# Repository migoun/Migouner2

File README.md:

# Migouner2
Second Mechanical Keyboard. This is a follow up of a keyboard, built 6 years ago: https://github.com/migoun/mechanical_keyboard_mac

Changes:
- STM32 MCU instead of Atmel Chip
- Addressable RGB LEDs backlight for each key (therefore the STM32)
- USB Micro port, to make this as low profile as possible
- Using JLCs Assembly service for one side of the board. 6 years ago, that didn't exist - or at least not for free. So i soldered everything back then
- First tries with printed 3D casings. Eventually CNC machining at a later stage

This time i start with a dev board, instead the whole keyboard:

**Front**

**Back**

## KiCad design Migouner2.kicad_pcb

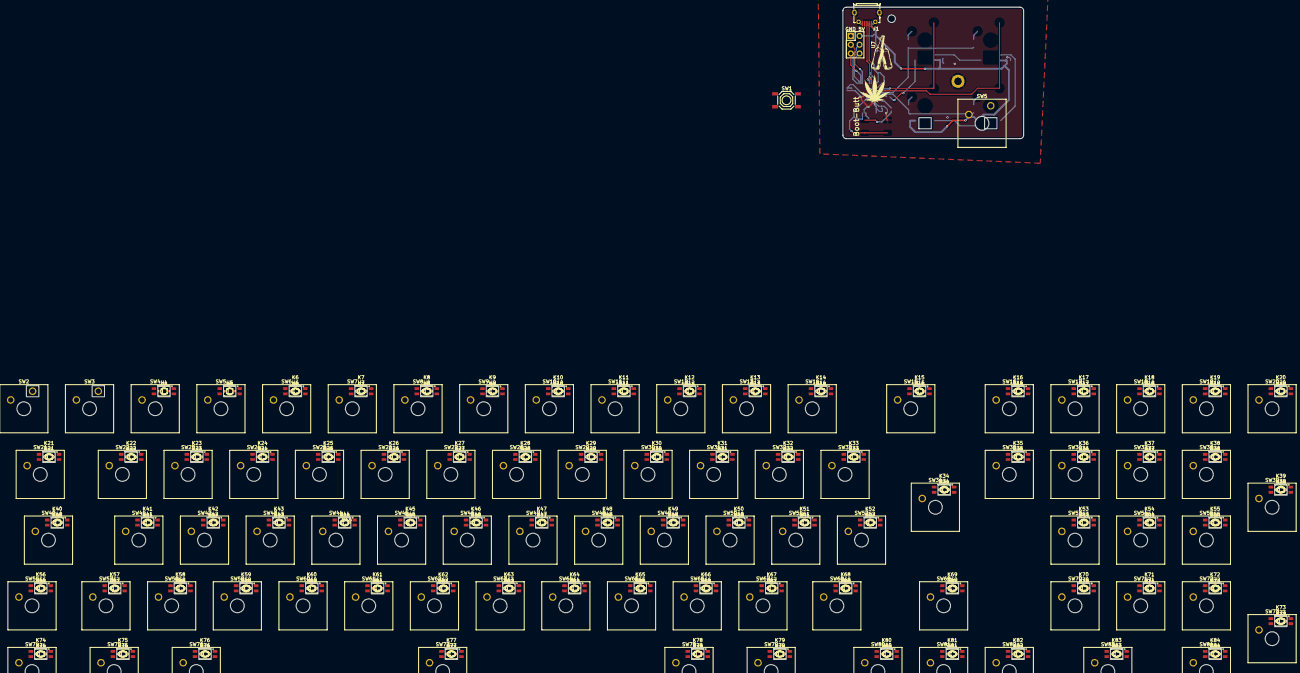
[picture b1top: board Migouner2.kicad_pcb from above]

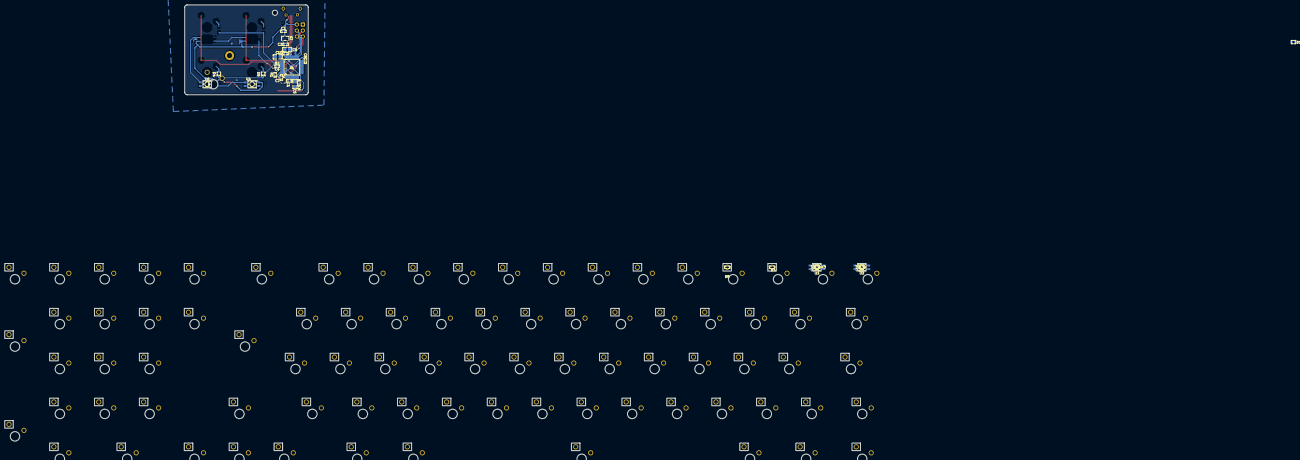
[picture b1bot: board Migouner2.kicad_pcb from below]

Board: 2 copper layers, 365.6 x 189.1 mm, 355 parts (27 on the bottom side), 204 nets.

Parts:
C1, C7, C8, C10: 100nF; C0402
C2, C3, C6: 1uF; C0402
C4, C9: 4.7uF; C0805
C5: 10nF; C0805
D1: ESDA7P60-1U1M; D1610-RD
D2, D4, D5, D6, D7, D8, D9, D10, D11, D12, D13, D14, D15, D16, D17, D18, D19, D20, D21, D23, D24, D25, D26, D27, D28, D29, D30, D31, D32, D33, D34, D35, D36, D37, D38, D39, D40, D42, D43, D44, D45, D46, D47, D48, D49, D50, D51, D52, D53, D54, D55, D56, D58, D59, D60, D61, D62, D63, D64, D65, D66, D67, D68, D69, D70, D71, D72, D73, D74, D76, D77, D78, D79, D80, D81, D82, D83, D84: A; SOD-323_L1.8-W1.3-LS2.5-RD
D3, D22, D41, D57, D75: S; SOD-323_L1.8-W1.3-LS2.5-RD
D4#2: W; SOD-323_L1.8-W1.3-LS2.5-RD
D5#2: D; SOD-323_L1.8-W1.3-LS2.5-RD
J1: USB_B_Micro; MICRO-USB-SMD_MICROXNJ
K2, K3, K4, K5, K6, K7, K8, K9, K10, K11, K12, K13, K14, K15, K16, K17, K18, K19, K20, K21, K22, K23, K24, K25, K26, K27, K28, K29, K30, K31, K32, K33, K34, K35, K36, K37, K38, K39, K40, K41, K42, K43, K44, K45, K46, K47, K48, K49, K50, K51, K52, K53, K54, K55, K56, K57, K58, K59, K60, K61, K62, K63, K64, K65, K66, K67, K68, K69, K70, K71, K72, K73, K74, K75, K76, K77, K78, K79, K80, K81, K82, K83, K84: 100nF; C0402
R1: 10K; R0402
R2: 470; R0402
SW1: Boot Switch; SW-SMD_4P-L5.1-W5.1-P3.70-LS6.5-TL-2
SW2: Esc; SW_Cherry_MX_1.00u_Plate
SW3: ! 1; SW_Cherry_MX_1.00u_Plate
SW4: " 2; SW_Cherry_MX_1.00u_Plate
SW5: £ 3; SW_Cherry_MX_1.00u_Plate
SW5#2, SW23: W; SW_Cherry_MX_1.00u_Plate
SW6: $ 4; SW_Cherry_MX_1.00u_Plate
SW7: % 5; SW_Cherry_MX_1.00u_Plate
SW8: ^ 6; SW_Cherry_MX_1.00u_Plate
SW9: & 7; SW_Cherry_MX_1.00u_Plate
SW10: * 8; SW_Cherry_MX_1.00u_Plate
SW11: ( 9; SW_Cherry_MX_1.00u_Plate
SW12: ) 0; SW_Cherry_MX_1.00u_Plate
SW13: _ -; SW_Cherry_MX_1.00u_Plate
SW14: + =; SW_Cherry_MX_1.00u_Plate
SW15: Backspace; SW_Cherry_MX_2.00u_Plate
SW16: Insert; SW_Cherry_MX_1.00u_Plate
SW17: %; SW_Cherry_MX_1.00u_Plate
SW18: /; SW_Cherry_MX_1.00u_Plate
SW19: *; SW_Cherry_MX_1.00u_Plate
SW20: -; SW_Cherry_MX_1.00u_Plate
SW21: Tab; SW_Cherry_MX_1.50u_Plate
SW22: Q; SW_Cherry_MX_1.00u_Plate
SW24: E; SW_Cherry_MX_1.00u_Plate
SW25: R; SW_Cherry_MX_1.00u_Plate
SW26: T; SW_Cherry_MX_1.00u_Plate
SW27: Y; SW_Cherry_MX_1.00u_Plate
SW28: U; SW_Cherry_MX_1.00u_Plate
SW29: I; SW_Cherry_MX_1.00u_Plate
SW30: O; SW_Cherry_MX_1.00u_Plate
SW31: P; SW_Cherry_MX_1.00u_Plate
SW32: { [; SW_Cherry_MX_1.00u_Plate
SW33: } ]; SW_Cherry_MX_1.00u_Plate
SW34: Enter; SW_Cherry_MX_ISOEnter_Plate
SW35: Delete; SW_Cherry_MX_1.00u_Plate
SW36: 7 Home; SW_Cherry_MX_1.00u_Plate
SW37: 8 ↑; SW_Cherry_MX_1.00u_Plate
SW38: 9 PgUp; SW_Cherry_MX_1.00u_Plate
SW39: +; SW_Cherry_MX_2.00u_Vertical_Plate
SW40: Caps Lock; SW_Cherry_MX_1.75u_Plate
SW41: A; SW_Cherry_MX_1.00u_Plate
SW42: S; SW_Cherry_MX_1.00u_Plate
SW43: D; SW_Cherry_MX_1.00u_Plate
SW44: F; SW_Cherry_MX_1.00u_Plate
SW45: G; SW_Cherry_MX_1.00u_Plate
SW46: H; SW_Cherry_MX_1.00u_Plate
SW47: J; SW_Cherry_MX_1.00u_Plate
SW48: K; SW_Cherry_MX_1.00u_Plate
SW49: L; SW_Cherry_MX_1.00u_Plate
SW50: : ;; SW_Cherry_MX_1.00u_Plate
SW51: @ '; SW_Cherry_MX_1.00u_Plate
SW52: ~ #; SW_Cherry_MX_1.00u_Plate
SW53: 4 ←; SW_Cherry_MX_1.00u_Plate
SW54: 5; SW_Cherry_MX_1.00u_Plate
SW55: 6 →; SW_Cherry_MX_1.00u_Plate
SW56, SW68: Shift; SW_Cherry_MX_1.25u_Plate
SW57: | \; SW_Cherry_MX_1.00u_Plate
SW58: Z; SW_Cherry_MX_1.00u_Plate
SW59: X; SW_Cherry_MX_1.00u_Plate
SW60: C; SW_Cherry_MX_1.00u_Plate
SW61: V; SW_Cherry_MX_1.00u_Plate
SW62: B; SW_Cherry_MX_1.00u_Plate
SW63: N; SW_Cherry_MX_1.00u_Plate
SW64: M; SW_Cherry_MX_1.00u_Plate
SW65: < ,; SW_Cherry_MX_1.00u_Plate
SW66: > .; SW_Cherry_MX_1.00u_Plate
SW67: ? /; SW_Cherry_MX_1.00u_Plate
SW69: ↑; SW_Cherry_MX_1.00u_Plate
SW70: 1 End; SW_Cherry_MX_1.00u_Plate
SW71: 2 ↓; SW_Cherry_MX_1.00u_Plate
SW72: 3 PgDn; SW_Cherry_MX_1.00u_Plate
SW73: Enter; SW_Cherry_MX_2.00u_Vertical_Plate
SW74: Ctrl; SW_Cherry_MX_1.25u_Plate
SW75: Win; SW_Cherry_MX_1.25u_Plate
SW76: Alt; SW_Cherry_MX_1.25u_Plate
SW77: SW_Cherry_MX_6.25u_Plate
SW78: AltGr; SW_Cherry_MX_1.25u_Plate
SW79: Fn; SW_Cherry_MX_1.25u_Plate
SW80: ←; SW_Cherry_MX_1.00u_Plate
SW81: ↓; SW_Cherry_MX_1.00u_Plate
SW82: →; SW_Cherry_MX_1.00u_Plate
SW83: 0 Ins; SW_Cherry_MX_2.00u_Plate
SW84: . Del; SW_Cherry_MX_1.00u_Plate
U2, U3, U4, U5, U6, U7, U8, U9, U10, U11, U12, U13, U14, U15, U16, U17, U18, U19, U20, U21, U22, U23, U24, U25, U26, U27, U28, U29, U30, U31, U32, U33, U34, U35, U36, U37, U38, U39, U40, U41, U42, U43, U44, U45, U46, U47, U48, U49, U50, U51, U52, U53, U54, U55, U56, U57, U58, U59, U60, U61, U62, U63, U64, U65, U66, U67, U68, U69, U70, U71, U72, U73, U74, U75, U76, U77, U78, U79, U80, U81, U82, U83, U84: LED-SMD_L3.2-W2.8-TR
U4#2: D; LED-SMD_L3.2-W2.8-TR
U6#2: W; LED-SMD_L3.2-W2.8-TR
U7#2: ZX-PZ2.54-2-5PZZ; HDR-TH_6P-P2.54-V-M-R2-C3-S2.54-1
X1: STM32F072CBT6; LQFP-48_L7.0-W7.0-P0.50-LS9.0-BL
X2: XC6206P332MR-G; SOT-23-3_L2.9-W1.6-P1.90-LS2.8-BR

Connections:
+3.3V: C3.1, C4.1, C5.1, C6.1, C7.1, C8.1, C9.1, C10.1, SW1.1 (A), SW1.2 (B), X1.1 (VBAT), X1.9 (VDDA), X1.24 (VDD), X1.36 (VDDIO2), X1.48 (VDD), X2.2 (VO)
+5V: C2.1, D1.1 (C), J1.1 (VBUS), K2.1, K3.1, K4.1, K5.1, K6.1, K7.1, K8.1, K9.1, K10.1, K11.1, K12.1, K13.1, K14.1, K15.1, K16.1, K17.1, K18.1, K19.1, K20.1, K21.1, K22.1, K23.1, K24.1, K25.1, K26.1, K27.1, K28.1, K29.1, K30.1, K31.1, K32.1, K33.1, K34.1, K35.1, K36.1, K37.1, K38.1, K39.1, K40.1, K41.1, K42.1, K43.1, K44.1, K45.1, K46.1, K47.1, K48.1, K49.1, K50.1, K51.1, K52.1, K53.1, K54.1, K55.1, K56.1, K57.1, K58.1, K59.1, K60.1, K61.1, K62.1, K63.1, K64.1, K65.1, K66.1, K67.1, K68.1, K69.1, K70.1, K71.1, K72.1, K73.1, K74.1, K75.1, K76.1, K77.1, K78.1, K79.1, K80.1, K81.1, K82.1, K83.1, K84.1, U4#2.1 (VDD), U6#2.1 (VDD), U7#2.2, U74.1 (VDD), U75.1 (VDD), U76.1 (VDD), U77.1 (VDD), U78.1 (VDD), U79.1 (VDD), U80.1 (VDD), U81.1 (VDD), U82.1 (VDD), U83.1 (VDD), U84.1 (VDD), X2.3 (VI)
/Keyboard Matrix/Col0: SW2.1, SW21.1, SW40.1, SW56.1, SW74.1, X1.41 (PB5)
/Keyboard Matrix/Col1: SW3.1, SW5#2.1, SW22.1, SW41.1, SW57.1, SW75.1, X1.40 (PB4)
/Keyboard Matrix/Col2: SW4.1, SW23.1, SW42.1, SW58.1, SW76.1, X1.39 (PB3)
/Keyboard Matrix/Col3: SW5.1, SW24.1, SW43.1, SW59.1, X1.38 (PA15)
/Keyboard Matrix/Col4: SW6.1, SW25.1, SW44.1, SW60.1, X1.37 (PA14)
/Keyboard Matrix/Col5: SW7.1, SW26.1, SW45.1, SW61.1, X1.34 (PA13)
/Keyboard Matrix/Col6: SW8.1, SW27.1, SW46.1, SW62.1, SW77.1, X1.31 (PA10)
/Keyboard Matrix/Col7: SW9.1, SW28.1, SW47.1, SW63.1, X1.30 (PA9)
/Keyboard Matrix/Col8: SW10.1, SW29.1, SW48.1, SW64.1, X1.29 (PA8)
/Keyboard Matrix/Col9: SW11.1, SW30.1, SW49.1, SW65.1, X1.28 (PB15)
/Keyboard Matrix/Col10: SW12.1, SW31.1, SW50.1, SW66.1, SW78.1, X1.27 (PB14)
/Keyboard Matrix/Col11: SW13.1, SW32.1, SW51.1, SW67.1, SW79.1, X1.26 (PB13)
/Keyboard Matrix/Col12: SW14.1, SW33.1, SW52.1, SW68.1, SW80.1, X1.25 (PB12)
/Keyboard Matrix/Col13: SW15.1, SW34.1, SW69.1, SW81.1, X1.11 (PA1)
/Keyboard Matrix/Col14: SW16.1, SW35.1, SW82.1, X1.12 (PA2)
/Keyboard Matrix/Col15: SW17.1, SW36.1, SW53.1, SW70.1, SW83.1, X1.13 (PA3)
/Keyboard Matrix/Col16: SW18.1, SW37.1, SW54.1, SW71.1, X1.14 (PA4)
/Keyboard Matrix/Col17: SW19.1, SW38.1, SW55.1, SW72.1, SW84.1, X1.15 (PA5)
/Keyboard Matrix/Col18: SW20.1, SW39.1, SW73.1, X1.16 (PA6)
/Keyboard Matrix/Row0: D2.1, D3.1, D4.1, D5.1, D6.1, D7.1, D8.1, D9.1, D10.1, D11.1, D12.1, D13.1, D14.1, D15.1, D16.1, D17.1, D18.1, D19.1, D20.1, X1.10 (PA0)
/Keyboard Matrix/Row1: D4#2.1, D5#2.1, D21.1, D22.1, D23.1, D24.1, D25.1, D26.1, D27.1, D28.1, D29.1, D30.1, D31.1, D32.1, D33.1, D34.1, D35.1, D36.1, D37.1, D38.1, D39.1, X1.46 (PB9)
/Keyboard Matrix/Row2: D40.1, D41.1, D42.1, D43.1, D44.1, D45.1, D46.1, D47.1, D48.1, D49.1, D50.1, D51.1, D52.1, D53.1, D54.1, D55.1, X1.45 (PB8)
/Keyboard Matrix/Row3: D56.1, D57.1, D58.1, D59.1, D60.1, D61.1, D62.1, D63.1, D64.1, D65.1, D66.1, D67.1, D68.1, D69.1, D70.1, D71.1, D72.1, D73.1, X1.43 (PB7)
/Keyboard Matrix/Row4: D74.1, D75.1, D76.1, D77.1, D78.1, D79.1, D80.1, D81.1, D82.1, D83.1, D84.1, X1.42 (PB6)
/RGB LEDs/LED_Control: R2.1, X1.17 (PA7)
/STM32/Boot: SW1.4 (D), X1.44 (BOOT0)
/STM32/USB D+: J1.3 (D+), X1.33 (PA12/USB+)
/STM32/USB D-: J1.2 (D-), X1.32 (PA11/USB-)
GND: C1.1, C2.2, C3.2, C4.2, C5.2, C6.2, C7.2, C8.2, C9.2, C10.2, D1.2 (A), J1.5 (GND), J1.6 (SH1), J1.7 (SH2), J1.8 (SH3), J1.9 (SH4), K2.2, K3.2, K4.2, K5.2, K6.2, K7.2, K8.2, K9.2, K10.2, K11.2, K12.2, K13.2, K14.2, K15.2, K16.2, K17.2, K18.2, K19.2, K20.2, K21.2, K22.2, K23.2, K24.2, K25.2, K26.2, K27.2, K28.2, K29.2, K30.2, K31.2, K32.2, K33.2, K34.2, K35.2, K36.2, K37.2, K38.2, K39.2, K40.2, K41.2, K42.2, K43.2, K44.2, K45.2, K46.2, K47.2, K48.2, K49.2, K50.2, K51.2, K52.2, K53.2, K54.2, K55.2, K56.2, K57.2, K58.2, K59.2, K60.2, K61.2, K62.2, K63.2, K64.2, K65.2, K66.2, K67.2, K68.2, K69.2, K70.2, K71.2, K72.2, K73.2, K74.2, K75.2, K76.2, K77.2, K78.2, K79.2, K80.2, K81.2, K82.2, K83.2, K84.2, R1.1, U2.3 (GND), U3.3 (GND), U4.3 (GND), U4#2.3 (GND), U5.3 (GND), U6.3 (GND), U6#2.3 (GND), U7.3 (GND), U7#2.1, U8.3 (GND), U9.3 (GND), U10.3 (GND), U11.3 (GND), U12.3 (GND), U13.3 (GND), U14.3 (GND), U15.3 (GND), U16.3 (GND), U17.3 (GND), U18.3 (GND), U19.3 (GND), U20.3 (GND), X1.8 (VSSA), X1.23 (VSS), X1.35 (VSS), X1.47 (VSS), X2.1 (GND)
unnamed: D2.2, SW2.2
unnamed: D3.2, SW3.2
unnamed: D4.2, D4#2.2, SW4.2, SW5#2.2
unnamed: D5.2, D5#2.2, SW5.2
unnamed: D6.2, SW6.2
unnamed: D7.2, SW7.2
unnamed: D8.2, SW8.2
unnamed: D9.2, SW9.2
unnamed: D10.2, SW10.2
unnamed: D11.2, SW11.2
unnamed: D12.2, SW12.2
unnamed: D13.2, SW13.2
unnamed: D14.2, SW14.2
unnamed: D15.2, SW15.2
unnamed: D16.2, SW16.2
unnamed: D17.2, SW17.2
unnamed: D18.2, SW18.2
unnamed: D19.2, SW19.2
unnamed: D20.2, SW20.2
unnamed: D21.2, SW21.2
unnamed: D22.2, SW22.2
unnamed: D23.2, SW23.2
unnamed: D24.2, SW24.2
unnamed: D25.2, SW25.2
unnamed: D26.2, SW26.2
unnamed: D27.2, SW27.2
unnamed: D28.2, SW28.2
unnamed: D29.2, SW29.2
unnamed: D30.2, SW30.2
unnamed: D31.2, SW31.2
unnamed: D32.2, SW32.2
unnamed: D33.2, SW33.2
unnamed: D34.2, SW34.2
unnamed: D35.2, SW35.2
unnamed: D36.2, SW36.2
unnamed: D37.2, SW37.2
unnamed: D38.2, SW38.2
unnamed: D39.2, SW39.2
unnamed: D40.2, SW40.2
unnamed: D41.2, SW41.2
unnamed: D42.2, SW42.2
unnamed: D43.2, SW43.2
unnamed: D44.2, SW44.2
unnamed: D45.2, SW45.2
unnamed: D46.2, SW46.2
unnamed: D47.2, SW47.2
unnamed: D48.2, SW48.2
unnamed: D49.2, SW49.2
unnamed: D50.2, SW50.2
unnamed: D51.2, SW51.2
unnamed: D52.2, SW52.2
unnamed: D53.2, SW53.2
unnamed: D54.2, SW54.2
unnamed: D55.2, SW55.2
unnamed: D56.2, SW56.2
unnamed: D57.2, SW57.2
unnamed: D58.2, SW58.2
unnamed: D59.2, SW59.2
unnamed: D60.2, SW60.2
unnamed: D61.2, SW61.2
unnamed: D62.2, SW62.2
unnamed: D63.2, SW63.2
unnamed: D64.2, SW64.2
unnamed: D65.2, SW65.2
unnamed: D66.2, SW66.2
unnamed: D67.2, SW67.2
unnamed: D68.2, SW68.2
unnamed: D69.2, SW69.2
unnamed: D70.2, SW70.2
unnamed: D71.2, SW71.2
unnamed: D72.2, SW72.2
unnamed: D73.2, SW73.2
unnamed: D74.2, SW74.2
unnamed: D75.2, SW75.2
unnamed: D76.2, SW76.2
unnamed: D77.2, SW77.2
unnamed: D78.2, SW78.2
unnamed: D79.2, SW79.2
unnamed: D80.2, SW80.2
unnamed: D81.2, SW81.2
unnamed: D82.2, SW82.2
unnamed: D83.2, SW83.2
unnamed: D84.2, SW84.2
unnamed: R1.2, SW1.3 (C)
unnamed: R2.2, U2.4 (DIN)
unnamed: U2.2 (DOUT), U3.4 (DIN)
unnamed: U3.2 (DOUT), U4.4 (DIN)
unnamed: U4#2.4 (DIN), U6#2.2 (DOUT)
unnamed: U4.2 (DOUT), U5.4 (DIN)
unnamed: U5.2 (DOUT), U6.4 (DIN), U6#2.4 (DIN)
unnamed: U6.2 (DOUT), U7.4 (DIN)
unnamed: U7.2 (DOUT), U8.4 (DIN)
unnamed: U8.2 (DOUT), U9.4 (DIN)
unnamed: U9.2 (DOUT), U10.4 (DIN)
unnamed: U10.2 (DOUT), U11.4 (DIN)
unnamed: U2.1 (VDD), U3.1 (VDD), U4.1 (VDD), U5.1 (VDD), U6.1 (VDD), U7.1 (VDD), U8.1 (VDD), U9.1 (VDD), U10.1 (VDD), U11.1 (VDD), U12.1 (VDD), U13.1 (VDD), U14.1 (VDD), U15.1 (VDD), U16.1 (VDD), U17.1 (VDD), U18.1 (VDD), U19.1 (VDD), U20.1 (VDD), U21.1 (VDD), U22.1 (VDD), U23.1 (VDD), U24.1 (VDD), U25.1 (VDD), U26.1 (VDD), U27.1 (VDD), U28.1 (VDD), U29.1 (VDD), U30.1 (VDD), U31.1 (VDD), U32.1 (VDD), U33.1 (VDD), U34.1 (VDD), U35.1 (VDD), U36.1 (VDD), U37.1 (VDD), U38.1 (VDD), U39.1 (VDD)
unnamed: U11.2 (DOUT), U12.4 (DIN)
unnamed: U12.2 (DOUT), U13.4 (DIN)
unnamed: U13.2 (DOUT), U14.4 (DIN)
unnamed: U14.2 (DOUT), U15.4 (DIN)
unnamed: U15.2 (DOUT), U16.4 (DIN)
unnamed: U16.2 (DOUT), U17.4 (DIN)
unnamed: U17.2 (DOUT), U18.4 (DIN)
unnamed: U18.2 (DOUT), U19.4 (DIN)
unnamed: U19.2 (DOUT), U20.4 (DIN)
unnamed: U20.2 (DOUT), U39.4 (DIN)
unnamed: U21.4 (DIN), U22.2 (DOUT)
unnamed: U21.2 (DOUT), U40.4 (DIN)
unnamed: U21.3 (GND), U22.3 (GND), U23.3 (GND), U24.3 (GND), U25.3 (GND), U26.3 (GND), U27.3 (GND), U28.3 (GND), U29.3 (GND), U30.3 (GND), U31.3 (GND), U32.3 (GND), U33.3 (GND), U34.3 (GND), U35.3 (GND), U36.3 (GND), U37.3 (GND), U38.3 (GND), U39.3 (GND), U40.3 (GND), U41.3 (GND), U42.3 (GND), U43.3 (GND), U44.3 (GND), U45.3 (GND), U46.3 (GND), U47.3 (GND), U48.3 (GND), U49.3 (GND), U50.3 (GND), U51.3 (GND), U52.3 (GND), U53.3 (GND), U54.3 (GND), U55.3 (GND)
unnamed: U22.4 (DIN), U23.2 (DOUT)
unnamed: U23.4 (DIN), U24.2 (DOUT)
unnamed: U24.4 (DIN), U25.2 (DOUT)
unnamed: U25.4 (DIN), U26.2 (DOUT)
unnamed: U26.4 (DIN), U27.2 (DOUT)
unnamed: U27.4 (DIN), U28.2 (DOUT)
unnamed: U28.4 (DIN), U29.2 (DOUT)
unnamed: U29.4 (DIN), U30.2 (DOUT)
unnamed: U30.4 (DIN), U31.2 (DOUT)
unnamed: U31.4 (DIN), U32.2 (DOUT)
unnamed: U32.4 (DIN), U33.2 (DOUT)
unnamed: U33.4 (DIN), U34.2 (DOUT)
unnamed: U34.4 (DIN), U35.2 (DOUT)
unnamed: U35.4 (DIN), U36.2 (DOUT)
unnamed: U36.4 (DIN), U37.2 (DOUT)
unnamed: U37.4 (DIN), U38.2 (DOUT)
unnamed: U38.4 (DIN), U39.2 (DOUT)
unnamed: U40.2 (DOUT), U41.4 (DIN)
unnamed: U40.1 (VDD), U41.1 (VDD), U42.1 (VDD), U43.1 (VDD), U44.1 (VDD), U45.1 (VDD), U46.1 (VDD), U47.1 (VDD), U48.1 (VDD), U49.1 (VDD), U50.1 (VDD), U51.1 (VDD), U53.1 (VDD), U54.1 (VDD), U55.1 (VDD), U56.1 (VDD), U57.1 (VDD), U58.1 (VDD), U59.1 (VDD), U60.1 (VDD), U61.1 (VDD), U62.1 (VDD), U63.1 (VDD), U64.1 (VDD), U65.1 (VDD), U66.1 (VDD), U67.1 (VDD), U68.1 (VDD), U69.1 (VDD), U70.1 (VDD), U71.1 (VDD), U72.1 (VDD), U73.1 (VDD)
unnamed: U41.2 (DOUT), U42.4 (DIN)
unnamed: U42.2 (DOUT), U43.4 (DIN)
unnamed: U43.2 (DOUT), U44.4 (DIN)
unnamed: U44.2 (DOUT), U45.4 (DIN)
unnamed: U45.2 (DOUT), U46.4 (DIN)
unnamed: U46.2 (DOUT), U47.4 (DIN)
unnamed: U47.2 (DOUT), U48.4 (DIN)
unnamed: U48.2 (DOUT), U49.4 (DIN)
unnamed: U49.2 (DOUT), U50.4 (DIN)
unnamed: U50.2 (DOUT), U51.4 (DIN)
unnamed: U51.2 (DOUT), U52.4 (DIN)
unnamed: U52.2 (DOUT), U53.4 (DIN)
unnamed: U53.2 (DOUT), U54.4 (DIN)
unnamed: U54.2 (DOUT), U55.4 (DIN)
unnamed: U55.2 (DOUT), U73.4 (DIN)
unnamed: U56.4 (DIN), U57.2 (DOUT)
unnamed: U56.2 (DOUT), U74.4 (DIN)
unnamed: U56.3 (GND), U57.3 (GND), U58.3 (GND), U59.3 (GND), U60.3 (GND), U61.3 (GND), U62.3 (GND), U63.3 (GND), U64.3 (GND), U65.3 (GND), U66.3 (GND), U67.3 (GND), U68.3 (GND), U69.3 (GND), U70.3 (GND), U71.3 (GND), U72.3 (GND), U73.3 (GND), U74.3 (GND), U75.3 (GND), U76.3 (GND), U77.3 (GND), U78.3 (GND), U79.3 (GND), U80.3 (GND), U81.3 (GND), U82.3 (GND), U83.3 (GND), U84.3 (GND)
unnamed: U57.4 (DIN), U58.2 (DOUT)
unnamed: U58.4 (DIN), U59.2 (DOUT)
unnamed: U59.4 (DIN), U60.2 (DOUT)
unnamed: U60.4 (DIN), U61.2 (DOUT)
unnamed: U61.4 (DIN), U62.2 (DOUT)
unnamed: U62.4 (DIN), U63.2 (DOUT)
unnamed: U63.4 (DIN), U64.2 (DOUT)
unnamed: U64.4 (DIN), U65.2 (DOUT)
unnamed: U65.4 (DIN), U66.2 (DOUT)
unnamed: U66.4 (DIN), U67.2 (DOUT)
unnamed: U67.4 (DIN), U68.2 (DOUT)
unnamed: U68.4 (DIN), U69.2 (DOUT)
unnamed: U69.4 (DIN), U70.2 (DOUT)
unnamed: U70.4 (DIN), U71.2 (DOUT)
unnamed: U71.4 (DIN), U72.2 (DOUT)
unnamed: U72.4 (DIN), U73.2 (DOUT)
unnamed: U74.2 (DOUT), U75.4 (DIN)
unnamed: U75.2 (DOUT), U76.4 (DIN)
unnamed: U76.2 (DOUT), U77.4 (DIN)
unnamed: U77.2 (DOUT), U78.4 (DIN)
unnamed: U78.2 (DOUT), U79.4 (DIN)
unnamed: U79.2 (DOUT), U80.4 (DIN)
unnamed: U80.2 (DOUT), U81.4 (DIN)
unnamed: U81.2 (DOUT), U82.4 (DIN)
unnamed: U82.2 (DOUT), U83.4 (DIN)
unnamed: U83.2 (DOUT), U84.4 (DIN)
unnamed: C1.2, X1.7 (NRST)

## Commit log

2024-08-18 Initial Commit. STM32 Devboard with 4 switches and RGB Leds
2024-08-18 Docs
2024-08-18 cleaned
2024-09-22 Update Migouner2.kicad_pcb, Migouner2.kicad_prl, Migouner2.kicad_pro, and 4 more files
2024-09-22 Corrected Devboard
2024-10-18 Case
2024-10-21 Board scripting
